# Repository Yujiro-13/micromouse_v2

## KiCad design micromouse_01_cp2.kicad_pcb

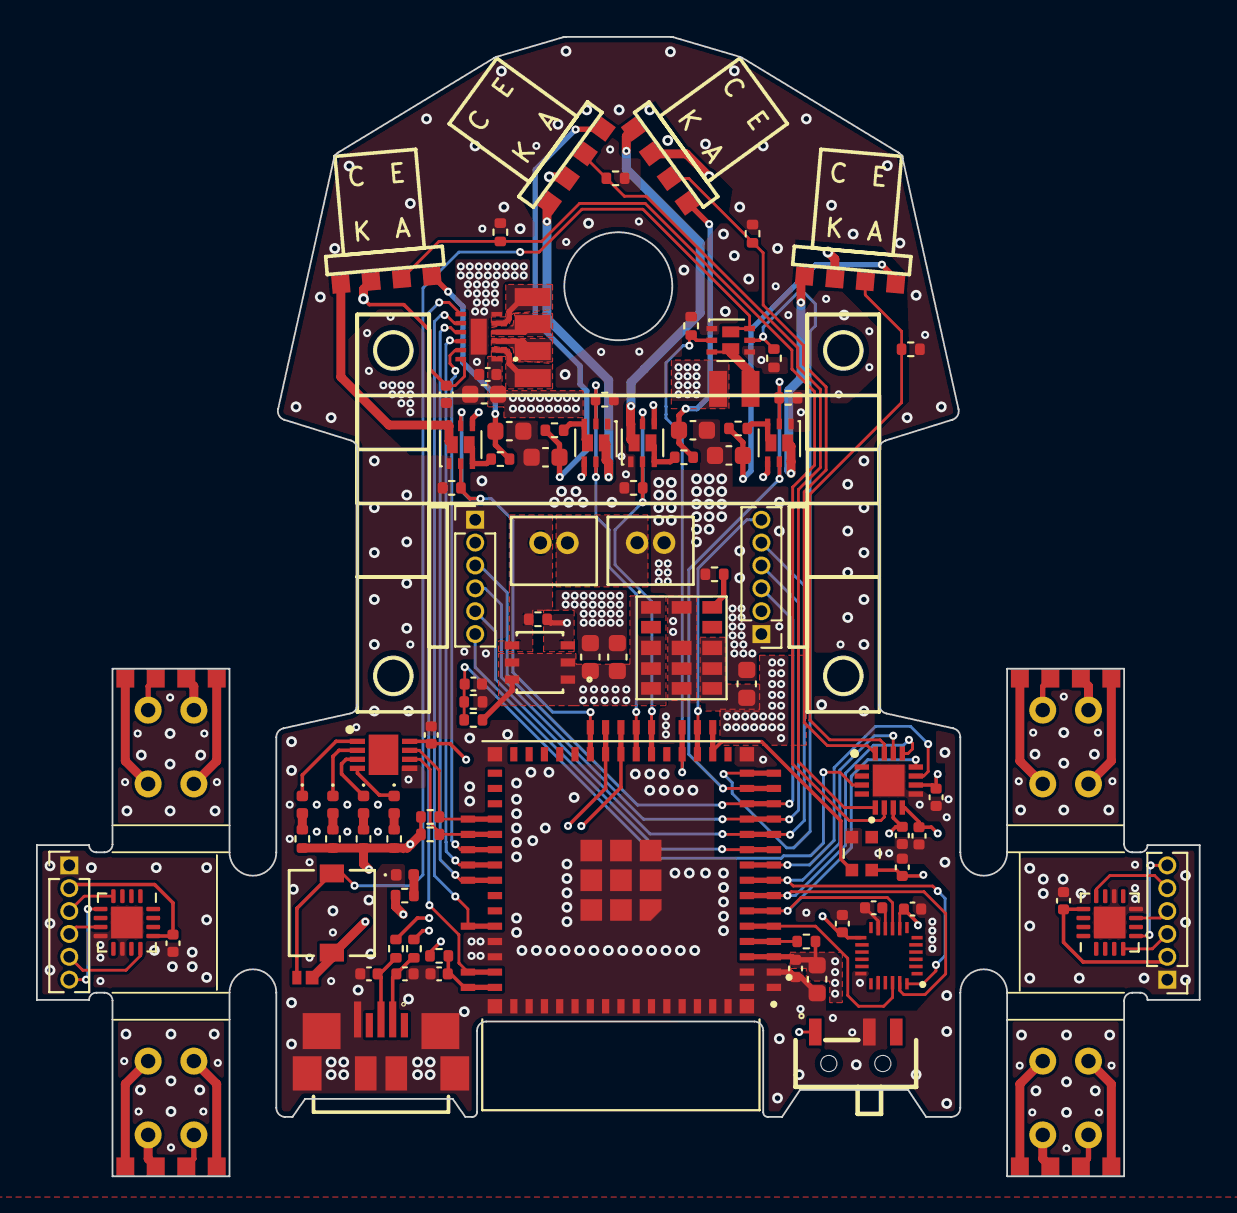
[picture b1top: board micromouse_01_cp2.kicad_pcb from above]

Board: 4 copper layers, 64.6 x 63.3 mm, 89 parts (0 on the bottom side), 66 nets.

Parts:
C2, C3: C_0402_1005Metric
C4, C8, C12, C17, C18, C19: 1u; C_0402_1005Metric
C5, C6, C7, C9, C11, C14, C15, C20, C24: 0.1u; C_0402_1005Metric
C10, C16, C23, C25, C27, C28, C29, C30: 22u; C_0603_1608Metric
C13: 10u; C_0603_1608Metric
D2: CCS15S40,L3F; SOD-963 CST2C_TOS
D4, D5, D6, D7: LED; LED_0402_1005Metric
D10: POWER; LED_0402_1005Metric
IC1: MPU-6500; QFN40P300X300X95-25N-D
IC2: DRV8835DSSR
IC3: ADS7066IRTER; QFN50P300X300X80-17N-D
IC4: PCA9632TK,118; SON50P300X300X100-9N-D
J1: ZX62R-B-5P_30_
J2: Fan+; Pad_1
J3: Fan-; Pad_1
J4, J5: Battery; CONN_B2B-ZRLFSN_JST
M1, M2: MK06-4.5
Q1: SiA910; Vishay_PowerPAK_SC70-6L_Dual
Q5, Q6, Q7, Q8: SiA519; Vishay_PowerPAK_SC70-6L_Dual
Q9: SSM6J808R_LXHF; TSOP6F_SSM6J_TOS
R1, R2: 0; R_0402_1005Metric
R3, R4, R14, R16: 10k; R_0402_1005Metric
R5, R6, R7, R10, R13, R15, R29: 47k; R_0402_1005Metric
R8, R9, R11, R12, R19: 2.4k; R_0402_1005Metric
R17: 1.3k; R_0402_1005Metric
R18: 1k; R_0402_1005Metric
R20: 620; R_0402_1005Metric
R21, R23, R25, R27: 22; R_0402_1005Metric
R22, R24, R26, R28: １ｋ; R_0402_1005Metric
SW1: SSSS810701
U1, U2: MA730; QFN-16-1EP_3x3mm_P0.5mm_EP1.75x1.75mm
U4: SMT-0440-S-R; SMT-0440-S-R_PUI
U5: WS2812-2020; LED_WS2812-2020
U7: LXDC55FAAA-203; CONV_LXDC55FAAA-203
U8, U9, U10, U11: LBR-127HLD
U12: ESP32-S3-MINI-1-N8; XCVR_ESP32-S3-MINI-1-N8

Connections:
+3V3: C4.1, C5.1, C6.1, C8.1, C9.1, C10.1, C11.1, C17.1, C18.1, C19.1, C20.1, C24.1, C25.1, D2.1 (K), IC1.8 (VDDIO), IC1.13 (VDD), IC2.12 (VCC), IC3.7 (AVDD), IC3.8 (REF), IC3.10 (DVDD), IC4.8 (VDD), Q5.4, Q6.4, Q7.4, Q8.4, R3.2, R4.1, R8.1, R9.1, R11.1, R12.1, R14.1, R16.1, R18.1, U1.13 (VDD), U2.13 (VDD), U4.1, U5.4 (VDD), U7.7 (VOUT_1), U7.8 (VOUT_2), U7.9 (VOUT_3), U12.3 (3V3)
+BATT: C13.2, C14.2, C16.1, C23.1, IC2.1 (VM), J2.1, Q9.1 (D1), Q9.2 (D2), Q9.5 (D3), Q9.6 (D4), R19.1, U7.1 (EN), U7.3 (VIN_1), U7.4 (VIN_2), U7.5 (VIN_3)
/BOOT: R4.2, U12.4 (IO0)
/EN: C12.2, R3.1, U12.45 (EN)
ADC_CS: IC3.11 (~CS), U12.9 (IO5)
BUZZER: Q1.2, R5.1, U12.19 (IO15)
ENCL_CS: U1.5 (~CS), U12.10 (IO6)
ENCR_CS: U2.5 (~CS), U12.18 (IO14)
ENC_CLK: U1.12 (SCLK), U2.12 (SCLK), U12.11 (IO7)
ENC_MISO: U1.7 (MISO), U2.7 (MISO), U12.12 (IO8)
ENC_MOSI: U1.4 (MOSI), U2.4 (MOSI), U12.13 (IO9)
FAN_PWM: Q1.5, R6.2, U12.15 (IO11)
GND: C2.2, C3.2, C4.2, C5.2, C6.2, C7.2, C8.2, C9.2, C10.2, C11.2, C12.1, C13.1, C14.1, C15.2, C16.2, C17.2, C18.2, C19.2, C20.2, C23.2, C24.2, C25.2, C27.2, C28.2, C29.2, C30.2, D10.1 (K), IC1.11 (FSYNC), IC1.18 (GND_1), IC1.20 (RESV_2), IC2.6 (GND_1), IC2.13 (GND_2), IC3.9 (GND), IC3.17 (EP), IC4.5 (VSS), J1.5 (GND), J1.6 (Shield), J1.7, J1.8, J1.9, J1.10, J1.11, J5.1, Q1.1, Q1.4, Q5.1, Q6.1, Q7.1, Q8.1, R5.2, R6.1, R7.2, R10.2, R13.2, R17.2, R20.2, R22.2, R24.2, R26.2, R28.2, R29.2, SW1.2 (B), U1.8 (GND), U1.10 (TEST), U1.17 (PAD), U2.8 (GND), U2.10 (TEST), U2.17 (PAD), U5.2 (GND), U7.6 (GND_1), U7.12 (GND_2), U7.13 (GND_3), U7.14 (GND_4), U12.1 (GND), U12.2 (GND__1), U12.42 (GND__2), U12.43 (GND__3), U12.46 (GND__4), U12.47 (GND__5), U12.48 (GND__6), U12.49 (GND__7), U12.50 (GND__8), U12.51 (GND__9), U12.52 (GND__10), U12.53 (GND__11), U12.54 (GND__12), U12.55 (GND__13), U12.56 (GND__14), U12.57 (GND__15), U12.58 (GND__16), U12.59 (GND__17), U12.60 (GND__18), U12.61 (GND__19), U12.61_1 (GND__20), U12.61_2 (GND__21), U12.61_3 (GND__22), U12.61_4 (GND__23), U12.61_5 (GND__24), U12.61_6 (GND__25), U12.61_7 (GND__26), U12.61_8 (GND__27), U12.62 (GND__28), U12.63 (GND__29), U12.64 (GND__30), U12.65 (GND__31)
IMU_CLK: IC1.23 (SCL_/_SCLK), IC3.13 (SCLK), U12.7 (IO3)
IMU_CS: IC1.22 (NCS), U12.5 (IO1)
IMU_MISO: IC1.9 (SDO_/_AD0), IC3.12 (SDO), U12.6 (IO2)
IMU_MOSI: IC1.24 (SDA_/_SDI), IC3.14 (SDI), U12.8 (IO4)
LED_FL: Q6.2, Q6.5, R10.1, U12.25 (IO21)
LED_FR: Q8.2, Q8.5, R29.1, U12.14 (IO10)
LED_L: Q5.2, Q5.5, R7.1, U12.22 (IO18)
LED_R: Q7.2, Q7.5, R13.1, U12.21 (IO17)
LED_SCL: IC4.6 (SCL), R16.2, U12.35 (IO39)
LED_SDA: IC4.7 (SDA), R14.2, U12.34 (IO38)
MOT1_ENBL: IC2.9 (AIN2_/_AENBL), U12.38 (IO42)
MOT1_PHASE: IC2.10 (AIN1_/_APHASE), U12.37 (IO41)
MOT2_ENBL: IC2.7 (BIN2_/_BENBL), U12.44 (IO46)
MOT2_PHASE: IC2.8 (BIN1_/_BPHASE), U12.41 (IO45)
MOT_MODE: IC2.11 (MODE), U12.36 (IO40)
NeoPixel: U5.3 (DI), U12.17 (IO13)
unnamed: C27.1, R21.2
unnamed: C28.1, R23.2
unnamed: C29.1, R25.2
unnamed: C30.1, R27.2
unnamed: D2.2 (A), Q1.6, U4.2
unnamed: D4.2 (A), R8.2
unnamed: D4.1 (K), IC4.1 (LED0)
unnamed: D5.2 (A), R9.2
unnamed: D5.1 (K), IC4.2 (LED1)
unnamed: D6.2 (A), R11.2
unnamed: D6.1 (K), IC4.3 (LED2)
unnamed: D7.2 (A), R12.2
unnamed: D7.1 (K), IC4.4 (LED3)
unnamed: D10.2 (A), R18.2
unnamed: C7.1, IC1.10 (REGOUT)
unnamed: IC2.2 (AOUT1), M1.1 (+)
unnamed: IC2.3 (AOUT2), M1.2 (-)
unnamed: IC2.4 (BOUT1), M2.1 (+)
unnamed: IC2.5 (BOUT2), M2.2 (-)
unnamed: C2.1, J1.3 (D+), R1.1
unnamed: C3.1, J1.2 (D-), R2.1
unnamed: J3.1, Q1.3
unnamed: J4.1, J5.2
unnamed: J4.2, Q9.4 (S), R15.1
unnamed: Q5.3, R21.1
unnamed: Q6.3, R23.1
unnamed: Q7.3, R25.1
unnamed: Q8.3, R27.1
unnamed: Q9.3 (G), R15.2, SW1.1 (A)
unnamed: R17.1, U7.11 (FB)
SENS_FL: IC3.6 (AIN7_/_GPIO7), R24.1
SENS_FR: IC3.15 (AIN0_/_GPIO0), R28.1
SENS_L: IC3.5 (AIN6_/_GPIO6), R22.1
SENS_R: IC3.16 (AIN1_/_GPIO1), R26.1
USB_D+: R1.2, U12.24 (IO20)
USB_D-: R2.2, U12.23 (IO19)
VBATT: C15.1, IC3.3 (AIN4_/_GPIO4), R19.2, R20.1

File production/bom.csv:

Designator,Footprint,Quantity,Value,LCSC Part #
"C10, C16, C23, C25, C27, C28, C29, C30",0603,8,22u,
"C11, C14, C15, C20, C24, C5, C6, C7, C9",0402,9,0.1u,
"C12, C17, C18, C19, C4, C8",0402,6,1u,
C13,0603,1,10u,
"C2, C3",0402,2,~,
D10,0402,1,POWER,
D2,SOD-963   CST2C_TOS,1,"CCS15S40,L3F",
"D4, D5, D6, D7",0402,4,LED,
IC1,QFN40P300X300X95-25N-D,1,MPU-6500,
IC2,DRV8835DSSR,1,DRV8835DSSR,
IC3,QFN50P300X300X80-17N-D,1,ADS7066IRTER,
IC4,SON50P300X300X100-9N-D,1,"PCA9632TK,118",
J1,ZX62R-B-5P_30_,1,~,
J2,Pad_1,1,Fan+,
J3,Pad_1,1,Fan-,
"J4, J5",CONN_B2B-ZRLFSN_JST,2,Battery,
"M1, M2",MK06-4.5,2,MK06-4.5,
Q1,Vishay_PowerPAK_SC70-6L_Dual,1,SiA910,
"Q5, Q6, Q7, Q8",Vishay_PowerPAK_SC70-6L_Dual,4,SiA519,
Q9,TSOP6F_SSM6J_TOS,1,SSM6J808R_LXHF,
"R1, R2",0402,2,0,
"R10, R13, R15, R29, R5, R6, R7",0402,7,47k,
"R11, R12, R19, R8, R9",0402,5,2.4k,
"R14, R16, R3, R4",0402,4,10k,
R17,0402,1,1.3k,
R18,0402,1,1k,
R20,0402,1,620,
"R21, R23, R25, R27",0402,4,22,
"R22, R24, R26, R28",0402,4,１ｋ,
SW1,SSSS810701,1,SSSS810701,
"U1, U2",QFN-16-1EP_3x3mm_P0.5mm_EP1.75x1.75mm,2,MA730,
U12,XCVR_ESP32-S3-MINI-1-N8,1,ESP32-S3-MINI-1-N8,
U4,SMT-0440-S-R_PUI,1,SMT-0440-S-R,
U5,LED_WS2812-2020,1,WS2812-2020,
U7,CONV_LXDC55FAAA-203,1,LXDC55FAAA-203,

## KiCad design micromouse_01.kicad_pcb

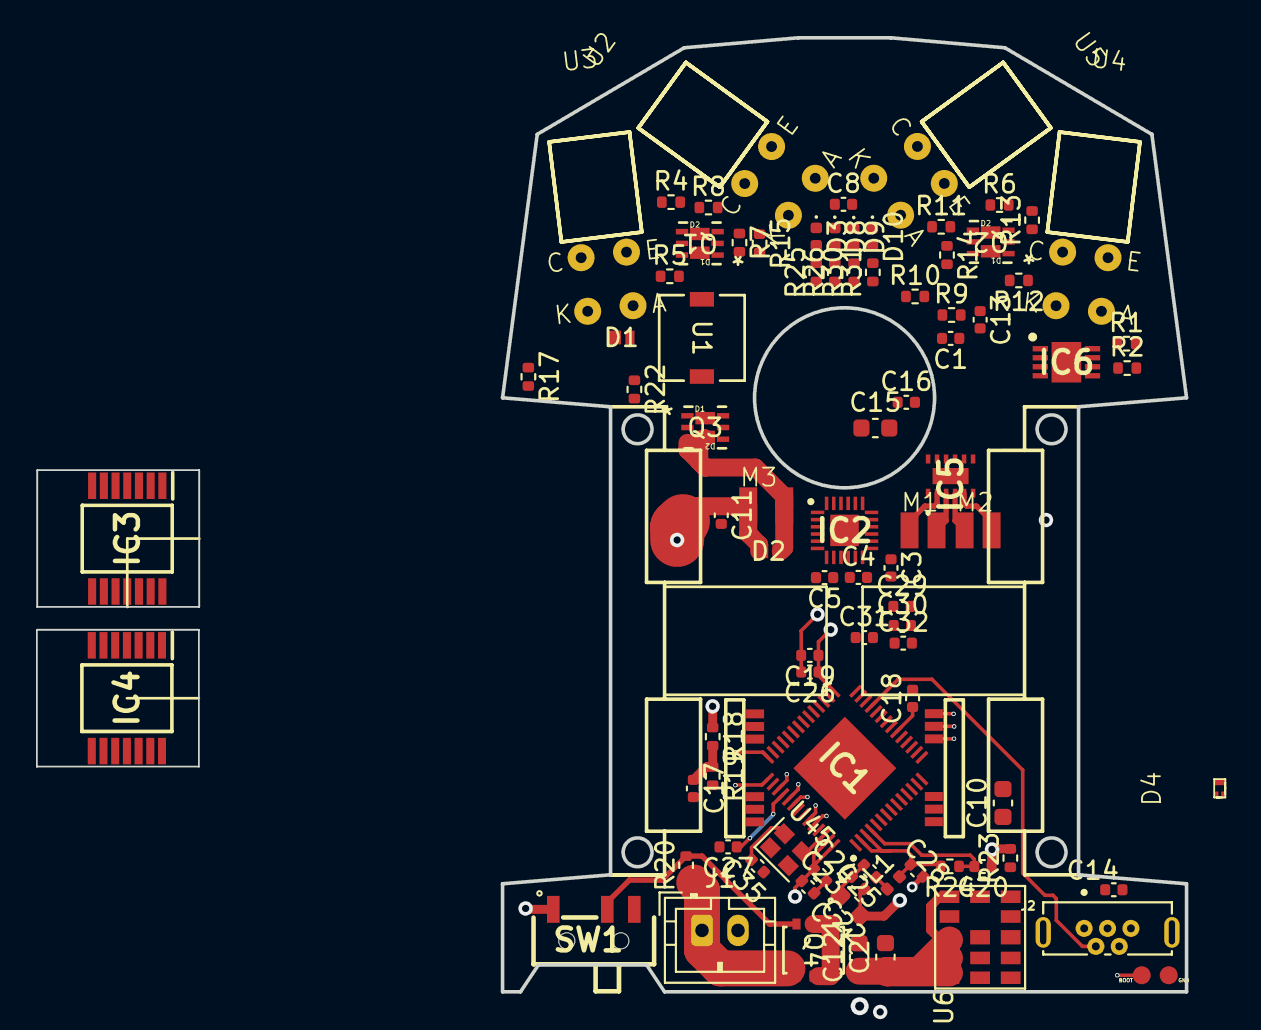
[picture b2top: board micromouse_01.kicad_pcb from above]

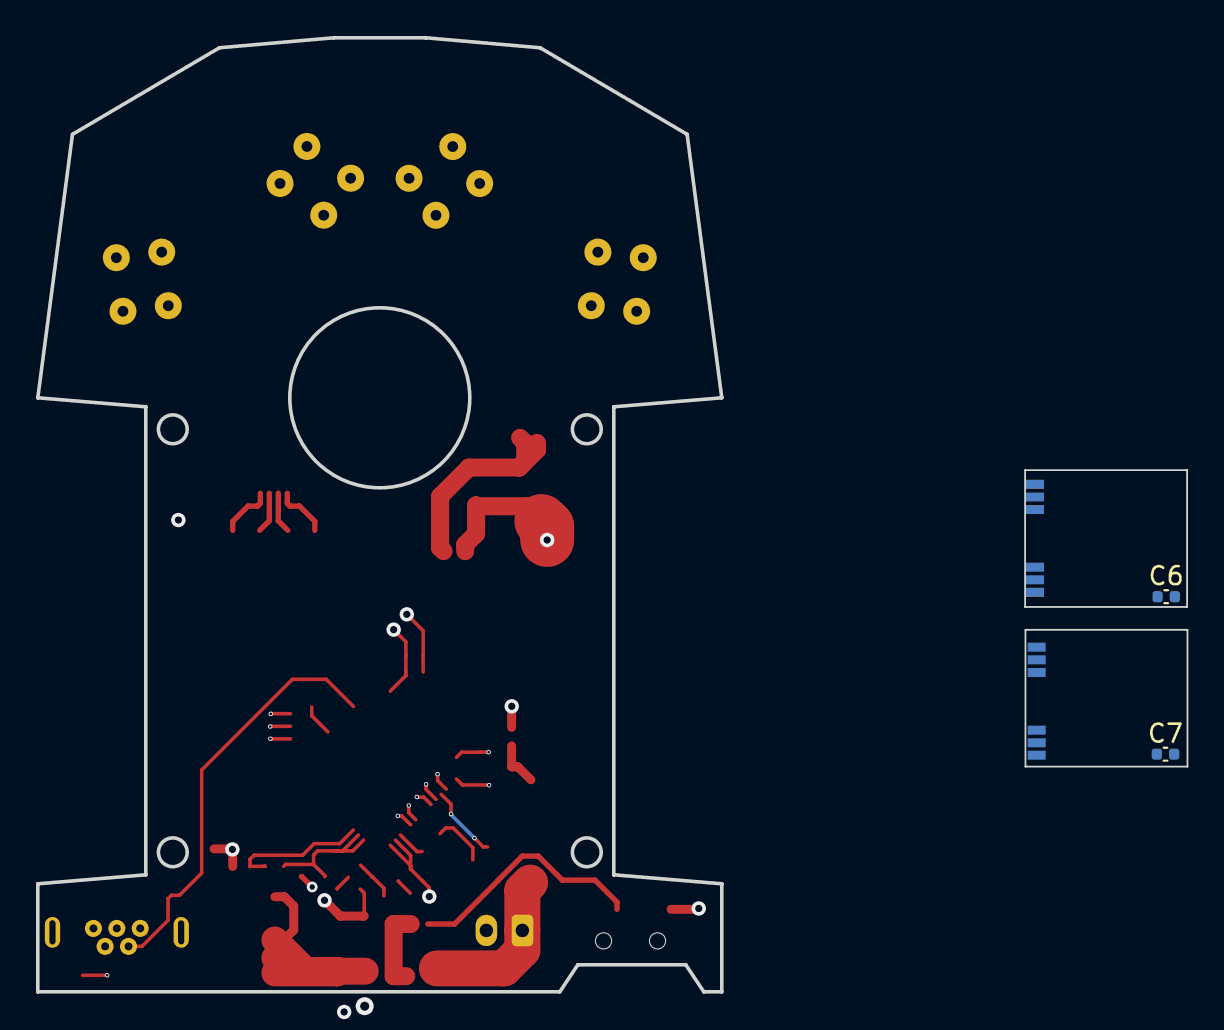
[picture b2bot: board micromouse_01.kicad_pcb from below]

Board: 4 copper layers, 38.0 x 53.0 mm, 88 parts (2 on the bottom side), 63 nets.

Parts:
C1, C3, C4, C5, C6, C7, C11, C13, C14, C16, C17, C18, C25, C26, C27, C28, C29, C30, C31, C32, C35: 0.1u; C_0402_1005Metric
C2, C10, C12: 22u; C_0603_1608Metric
C8, C19, C20, C22, C23: 1u; C_0402_1005Metric
C15, C21: 10u; C_0603_1608Metric
C24: 0.01u; C_0402_1005Metric
D1, D2: CCS15S40,L3F; SOD-963 CST2C_TOS
D3, D8, D9, D10: LED; LED_0402_1005Metric
D4: PESD3V3L2UM,315
IC1: ESP32-S3FH4R2; QFN40P700X700X90-57N-D
IC2: MPU-6500; QFN40P300X300X95-25N-D
IC3, IC4: AS5047P-ATSM; SOP65P640X120-14N
IC5: DRV8835DSSR
IC6: PCA9632TK,118; SON50P300X300X100-9N-D
J1: Conn_01x02; JST_PH_B2B-PH-K_1x02_P2.00mm_Vertical
J2: USB_B_Micro; WURTH_614105150721
L1: 2.0nH; L_0402_1005Metric
M1, M2: MK06-4.5
M3: Fan_Motor; MK06-4.5
Q1, Q2, Q3: MCM3400A-TP; DFN2020-6L_MCE
Q4: SSM6J808R_LXHF; TSOP6F_SSM6J_TOS
R1, R2, R18, R24: 10k; R_0402_1005Metric
R4, R8, R10, R14, R17, R20, R22: 47k; R_0402_1005Metric
R5, R7, R11, R13: 100; R_0402_1005Metric
R6, R9, R12, R15, R25, R26, R30, R31: 1k; R_0402_1005Metric
R19: 30k; R_0402_1005Metric
R23: 1.3k; R_0402_1005Metric
SW1: SSSS810701
U1: SMT-0440-S-R; SMT-0440-S-R_PUI
U2, U3, U4, U5: LBR-127HLD
U6: LXDC55FAAA-203; CONV_LXDC55FAAA-203
U45: RTV-104DF333-S-40.000-TR; Crystal_SMD_2016-4Pin_2.0x1.6mm

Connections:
+3V3: C1.1, C3.1, C5.1, C6.1, C7.1, C8.1, C10.1, C13.1, C18.1, C19.1, C21.1, C22.1, C23.1, C24.1, C25.1, C26.1, C27.1, C35.2, D1.1 (K), IC1.20 (VDD3P3_RTC), IC1.29 (VDD_SPI), IC1.46 (VDD3P3_CPU), IC1.55 (VDDA_1), IC1.56 (VDDA_2), IC2.8 (VDDIO), IC2.13 (VDD), IC3.11 (VDD), IC3.12 (VDD3V), IC4.11 (VDD), IC4.12 (VDD3V), IC5.12 (VCC), IC6.8 (VDD), L1.1, R1.1, R2.1, R25.1, R26.1, R30.1, R31.1, U1.1, U2.1, U2.4, U3.1, U3.4, U4.1, U4.4, U5.1, U5.4, U6.7 (VOUT_1), U6.8 (VOUT_2), U6.9 (VOUT_3), U45.4 (Vcc)
+BATT: C2.1, C11.1, C12.1, C15.2, C16.2, D2.1 (K), IC5.1 (VM), M3.1 (+), Q4.1 (D1), Q4.2 (D2), Q4.5 (D3), Q4.6 (D4), R18.1, U6.1 (EN), U6.3 (VIN_1), U6.4 (VIN_2), U6.5 (VIN_3)
BUZZER: IC1.43 (GPIO38), Q3.2 (G1), R17.1
ENC1_CS: IC1.6 (GPIO1), IC3.1 (CSN)
ENC2_CS: IC1.11 (GPIO6), IC4.1 (CSN)
ENC_CLK: IC1.15 (GPIO10), IC3.2 (CLK), IC4.2 (CLK)
ENC_MISO: IC1.16 (GPIO11), IC3.3 (MISO), IC4.3 (MISO)
ENC_MOSI: IC1.17 (GPIO12), IC3.4 (MOSI), IC4.4 (MOSI)
FAN_PWM: IC1.45 (MTDO), Q3.5 (G2), R22.1
GND: C1.2, C2.2, C3.2, C4.2, C5.2, C6.2, C7.2, C8.2, C10.2, C11.2, C12.2, C13.2, C14.2, C15.1, C16.1, C17.2, C18.2, C19.2, C20.1, C21.2, C22.2, C23.2, C24.2, C25.2, C26.2, C27.2, C28.2, C29.2, C30.2, C31.2, C32.2, C35.1, D4.3, IC1.57 (EP), IC2.11 (FSYNC), IC2.18 (GND_1), IC2.20 (RESV_2), IC2.25 (GND_2), IC3.5 (TEST), IC3.13 (GND), IC4.5 (TEST), IC4.13 (GND), IC5.6 (GND_1), IC5.13 (GND_2), IC6.5 (VSS), J1.2, J2.5 (GND), Q1.1, Q1.4, Q2.1 (S1), Q2.4 (S2), Q3.1 (S1), Q3.4 (S2), R4.2, R6.2, R8.2, R9.2, R10.2, R12.2, R14.2, R15.2, R17.2, R19.2, R22.2, R23.2, SW1.1 (A), U6.6 (GND_1), U6.12 (GND_2), U6.13 (GND_3), U6.14 (GND_4), U45.2 (GND)
IMU_CLK: IC1.23 (GPIO17), IC2.23 (SCL_/_SCLK)
IMU_CS: IC1.12 (GPIO7), IC2.22 (NCS)
IMU_MISO: IC1.24 (GPIO18), IC2.9 (SDO_/_AD0)
IMU_MOSI: IC1.27 (GPIO21), IC2.24 (SDA_/_SDI)
LED_FL: IC1.51 (GPIO45), Q1.5, R8.1
LED_FR: IC1.48 (MTMS), Q2.2 (G1), R10.1
LED_L: IC1.52 (GPIO46), Q1.2, R4.1
LED_R: IC1.47 (MTDI), Q2.5 (G2), R14.1
LED_SCL: IC1.18 (GPIO13), IC6.6 (SCL), R2.2
LED_SDA: IC1.19 (GPIO14), IC6.7 (SDA), R1.2
MOT1_ENBL: IC1.40 (GPIO35), IC5.9 (AIN2_/_AENBL)
MOT1_PHASE: IC1.41 (GPIO36), IC5.10 (AIN1_/_APHASE)
MOT2_ENBL: IC1.38 (GPIO33), IC5.7 (BIN2_/_BENBL)
MOT2_PHASE: IC1.39 (GPIO34), IC5.8 (BIN1_/_BPHASE)
MOT_MODE: IC1.42 (GPIO37), IC5.11 (MODE)
unnamed: D1.2 (A), Q3.6 (D1), U1.2
unnamed: D2.2 (A), M3.2 (-), Q3.3 (D2)
unnamed: D3.2 (A), R25.2
unnamed: D3.1 (K), IC6.1 (LED0)
unnamed: D8.2 (A), R26.2
unnamed: D8.1 (K), IC6.2 (LED1)
unnamed: D9.2 (A), R30.2
unnamed: D9.1 (K), IC6.3 (LED2)
unnamed: D10.2 (A), R31.2
unnamed: D10.1 (K), IC6.4 (LED3)
unnamed: C20.2, IC1.4 (CHIP_PU), R24.1
unnamed: C28.1, IC1.2 (VDD3P3_1), IC1.3 (VDD3P3_2), L1.2, R24.2
unnamed: IC1.54 (XTAL_P), U45.3 (OUT)
unnamed: C4.1, IC2.10 (REGOUT)
unnamed: IC5.2 (AOUT1), M1.1 (+)
unnamed: IC5.3 (AOUT2), M1.2 (-)
unnamed: IC5.4 (BOUT1), M2.1 (+)
unnamed: IC5.5 (BOUT2), M2.2 (-)
unnamed: J1.1, Q4.4 (S), R20.1
unnamed: C14.1, J2.1 (VBUS)
unnamed: Q1.3, R7.2
unnamed: Q1.6, R5.2
unnamed: Q2.6 (D1), R11.2
unnamed: Q2.3 (D2), R13.2
unnamed: Q4.3 (G), R20.2, SW1.2 (B)
unnamed: R5.1, U2.2
unnamed: R7.1, U3.2
unnamed: R11.1, U4.2
unnamed: R13.1, U5.2
unnamed: R23.1, U6.11 (FB)
SENS_FL: C31.1, IC1.9 (GPIO4), R9.1, U3.3
SENS_FR: C30.1, IC1.8 (GPIO3)
SENS_L: C32.1, IC1.10 (GPIO5), R6.1, U2.3
SENS_R: C29.1, IC1.7 (GPIO2), R15.1, U5.3
SE_S_FR: R12.1, U4.3
USB_D+: D4.2, IC1.26 (GPIO20), J2.3 (D+)
USB_D-: D4.1, IC1.25 (GPIO19), J2.2 (D-)
VBATT: C17.1, IC1.13 (GPIO8), R18.2, R19.1

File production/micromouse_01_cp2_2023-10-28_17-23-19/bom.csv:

Designator,Footprint,Quantity,Value,LCSC Part #
"C1, C11, C13, C14, C16, C17, C18, C25, C26, C27, C28, C29, C3, C30, C31, C32, C35, C4, C5, C6, C7",0402,21,0.1u,
"C10, C12, C2",0603,3,22u,
"C15, C21",0603,2,10u,
"C19, C20, C22, C23, C8",0402,5,1u,
C24,0402,1,0.01u,
"D1, D2",SOD-963   CST2C_TOS,2,"CCS15S40,L3F",
"D10, D3, D8, D9",0402,4,LED,
D4,"PESD3V3L2UM,315",1,"PESD3V3L2UM,315",
IC1,QFN40P700X700X90-57N-D,1,ESP32-S3FH4R2,
IC2,QFN40P300X300X95-25N-D,1,MPU-6500,
"IC3, IC4",SOP65P640X120-14N,2,AS5047P-ATSM,
IC5,DRV8835DSSR,1,DRV8835DSSR,
IC6,SON50P300X300X100-9N-D,1,"PCA9632TK,118",
J1,JST_PH_B2B-PH-K_1x02_P2.00mm_Vertical,1,Conn_01x02,
J2,WURTH_614105150721,1,USB_B_Micro,
L1,0402,1,2.0nH,
"M1, M2",MK06-4.5,2,MK06-4.5,
M3,MK06-4.5,1,Fan_Motor,
"Q1, Q2, Q3",DFN2020-6L_MCE,3,MCM3400A-TP,
Q4,TSOP6F_SSM6J_TOS,1,SSM6J808R_LXHF,
"R1, R18, R2, R24",0402,4,10k,
"R10, R14, R20, R4, R8",0402,5,47k,
"R11, R13, R5, R7",0402,4,100,
"R12, R15, R25, R26, R30, R31, R6, R9",0402,8,1k,
"R17, R22",0402,2, 47k,
R19,0402,1,30k,
R23,0402,1,1.3k,
SW1,SSSS810701,1,SSSS810701,
U1,SMT-0440-S-R_PUI,1,SMT-0440-S-R,
"U2, U3, U4, U5",LBR-127HLD,4,LBR-127HLD,
U6,CONV_LXDC55FAAA-203,1,LXDC55FAAA-203,
U7,Crystal_SMD_2016-4Pin_2.0x1.6mm,1,RTV-104DF333-S-40.000-TR,

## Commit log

2023-10-31 push
2023-10-31 [fix]アンテナ除去
2023-10-31 [fix]ブザー移動
2023-10-31 New commit
2023-10-31 [add]LED追加
2023-11-01 エンコーダ基板ビア打ち エラー修正
2023-11-02 エンコーダ基板修正 LBR-127HLDスルーホール修正
2023-11-02 ゾーンの優先度を修正
2023-11-03 エンコーダ基板シルク マイコンフットプリント位置修正
2023-11-04 [fix]ベタ除去
2023-11-04 エンコーダ基板シルク追加
2024-03-02 ブランチ作成前最終コミット
2024-03-09 Update symbol
2024-03-09 [update]けっこう線引いた
2024-03-14 エンコーダ基板変更前コミット
2024-03-16 とりあえず回路図完成
2024-03-17 パターン配線中
2024-03-17 ブランチ変更前コミット
2024-03-18 アンテナ除去中
2024-03-18 [add]3Dモデル追加
2024-03-19 アンテナ除去した
2024-03-19 [update]いい感じ
2024-03-29 PICO-1-N8R2用回路
2024-03-29 N8R8用回路（仮）
2024-04-13 バックアップファイルコミット
2024-04-13 [Add] .gitignore
2024-04-13 ipt iamファイルを除外
2024-04-24 add bom
2024-04-26 encoder footprint更新
2024-05-02 エンコーダ、モータパッド修正、エンコーダ差し込み穴修正
2024-05-02 [update]ADCと壁センサ周りを変更
2024-05-03 新しい部品乗せた
2024-05-05 PCB設計完了（仮）
2024-05-06 [fix]ブザー向きを修正
2024-05-06 Lipo接続パッド修正
2024-08-19 回路図完成 PCB配線途中
2024-08-19 Initial commit in ThinkPad PC
2024-08-20 change encoder footprint
2024-09-17 Added 3D model
2024-09-17 solve branch checkout error
2024-09-18 ノイズ除去仮終了
2024-09-25 未配線エラー解決
2024-09-25 メインボードとサブボードの結合完了
2024-09-26 サブボードの接続部調整
2024-10-01 stash
2024-10-06 [Fix]基板外形フィレット追加
2024-11-02 create BOM
2024-12-13 clear
